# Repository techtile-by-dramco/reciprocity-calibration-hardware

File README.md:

# Techtile PLL board ✅

This PCB was developed by Guus Leenders from KU Leuven, in collaboration with DRAMCO, with assistance from Jarne Van Mulders. The board is utilized in a distributed antenna or **Radioweave** infrastructure and delivers a phase-synchronous RF output to the USRP by means of a PPS and 10MHz signal. 

❗❗ This board is specifically designed for the **USRP B210** by Ettus. ❗❗

The PPS and 10MHz signals (coming from the octoclocks CDA2990) are amplified using on board buffers and are connected to the
* PLL IC (MAX287x) ❗❗ **--> allowing for ∿ phase synchronisation ∿**
* the flat cable connector (given that the raspberry pi also has access to these signals) ❗
* the input SMA connectors of the USRPs intself ❗❗
  * ** 10 MHz --> ∿ frequency synchronisation ∿ for internal (RF) PLLs**
  * ** PPS --> ⏰ time synchronisation ⏰**

The board is controlled via I2C commands and features a flat cable input connected to the RPI HAT (developed by DRAMCO) to drive the PLL output. The most important registers are displayed below.

###  PLL board general settings ⚙️

|Register name| byte |
|--|--|
|REGISTER_SETTINGS_DEVICE_ID            | 0x00 |
|REGISTER_SETTINGS_HARDWARE_VERSION     | 0x01 |
|REGISTER_SETTINGS_FIRMWARE_VERSION     | 0x02 |
|REGISTER_SETTINGS_SAVE_TO_EEPROM       | 0x03 |
|REGISTER_SETTINGS_PLL_REFERENCE_CLOCK  | 0x04 |
|REGISTER_SETTINGS_PLL_REFERENCE_DIVIDER| 0x06 |
|REGISTER_SETTINGS_LED_MODE             | 0x07 |
|REGISTER_SETTINGS_LED_BLINK_ON_TIME    | 0x08 |
|REGISTER_SETTINGS_LED_BLINK_OFF_TIME   | 0x09 |

###  PLL (MAX287x) settings ⚙️

|Register name| byte | Remarks |
|--|--|--|
|REGISTER_PLL_POWER                     | 0x10 | |
|REGISTER_PLL_FREQUENCY                 | 0x11 | 2 byte (uint16) |
|REGISTER_PLL_ENABLE_OUTPUT             | 0x13 | |
|REGISTER_PLL_LOCK_DETECTED             | 0x14 | Read only |
|REGISTER_PLL_MODE                      | 0x15 | Read only |

# Phase synchronisation in Techtile ToDo 📝
- Work further on python script to achieve phase-synchronised outputs with the B210 USRP. Validate and visualize the signals on the oscilloscope by using two separate setups consisting of RPI, USRP, PLL, PPS, and 10 MHz input.
- Current status ⏳ PENDING ⏳

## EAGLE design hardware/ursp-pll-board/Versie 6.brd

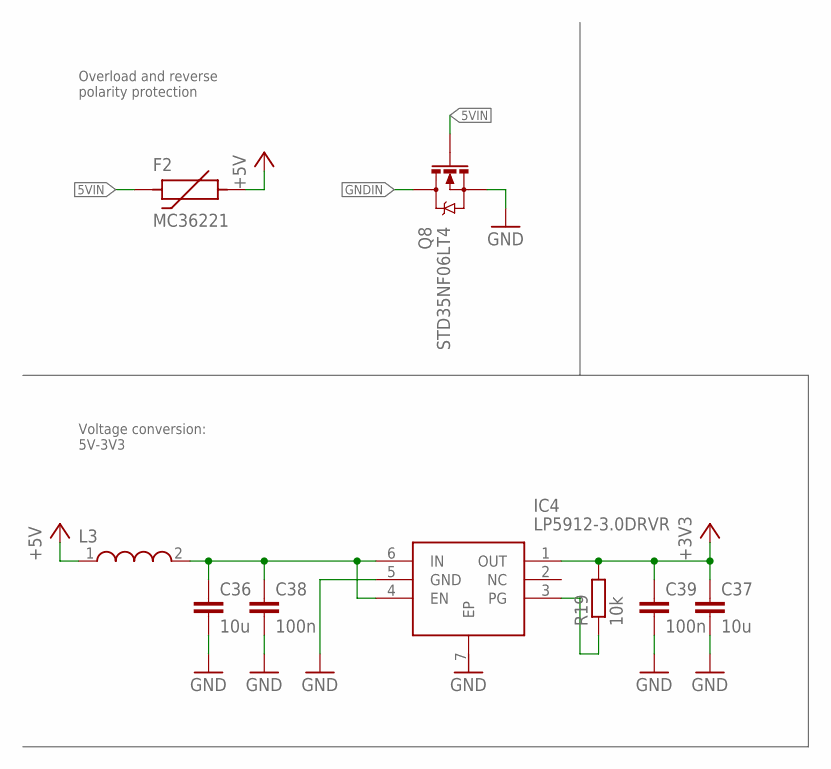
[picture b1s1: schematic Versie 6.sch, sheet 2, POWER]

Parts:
C36, C37: 10u; C0603
C38, C39: 100n; C0603
F2: MC36221; 1206
IC4: LP5912-3.0DRVR; SON65P200X200X80-7N
L3: WE-CBA_0603(WB/HS); WE-CBA_0603(W=2.2)
Q8: STD35NF06LT4; SOT23-3
R19: 10k; R0603

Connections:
5VIN: F2.P$1, Q8.1 (G); also elsewhere on the board
+3V3: C37.1, C39.1, IC4.1 (OUT), R19.2; also elsewhere on the board
+5V: F2.P$2, L3.1
GND: C36.2, C37.2, C38.2, C39.2, IC4.5 (GND), Q8.2 (S); also elsewhere on the board
GNDIN: Q8.3 (D); also elsewhere on the board
unnamed: C36.1, C38.1, IC4.4 (EN), IC4.6 (IN), L3.2
unnamed: IC4.3 (PG), R19.1

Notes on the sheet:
Overload and reverse polarity protection
Voltage conversion: 5V-3V3

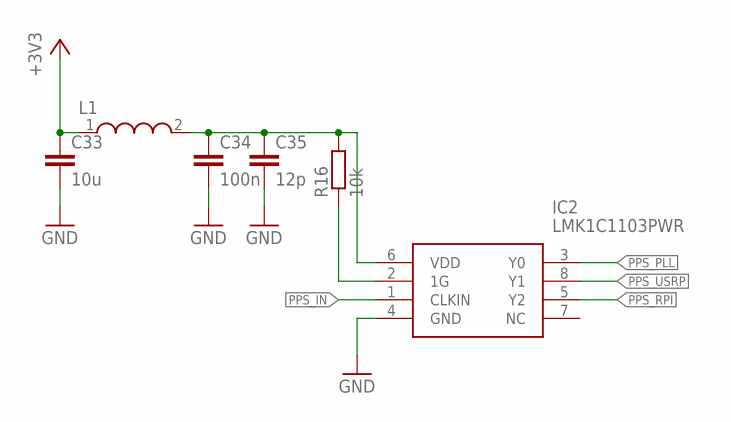
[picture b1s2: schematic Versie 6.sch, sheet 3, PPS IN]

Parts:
C33: 10u; C0603
C34: 100n; C0603
C35: 12p; C0603
IC2: LMK1C1103PWR; SOP65P640X120-8N
L1: WE-CBA_0603(WB/HS); WE-CBA_0603(W=2.2)
R16: 10k; R0603

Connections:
+3V3: C33.1, L1.1; also elsewhere on the board
GND: C33.2, C34.2, C35.2, IC2.4 (GND); also elsewhere on the board
unnamed: IC2.2 (1G), R16.1
unnamed: C34.1, C35.1, IC2.6 (VDD), L1.2, R16.2
PPS_IN: IC2.1 (CLKIN); also elsewhere on the board
PPS_PLL: IC2.3 (Y0); also elsewhere on the board
PPS_RPI: IC2.5 (Y2); also elsewhere on the board
PPS_USRP: IC2.8 (Y1); also elsewhere on the board

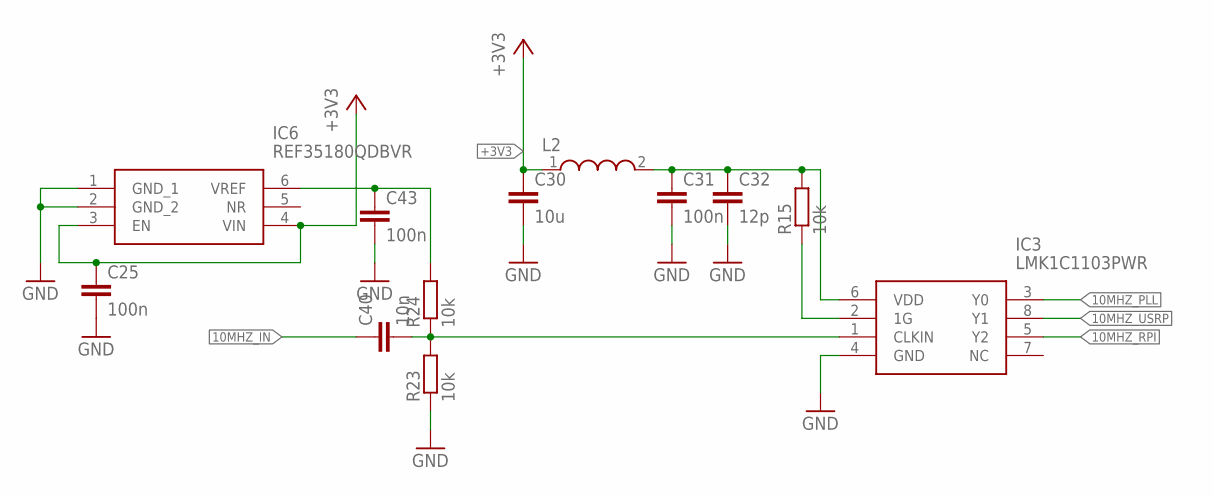
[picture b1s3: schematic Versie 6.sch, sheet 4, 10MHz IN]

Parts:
C25, C31, C43: 100n; C0603
C30: 10u; C0603
C32: 12p; C0603
C40: 10n; C0603
IC3: LMK1C1103PWR; SOP65P640X120-8N
IC6: REF35180QDBVR; SOT95P280X145-6N
L2: WE-CBA_0603(WB/HS); WE-CBA_0603(W=2.2)
R15, R23, R24: 10k; R0603

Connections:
10MHZ_IN: C40.1; also elsewhere on the board
10MHZ_PLL: IC3.3 (Y0); also elsewhere on the board
10MHZ_RPI: IC3.5 (Y2); also elsewhere on the board
10MHZ_USRP: IC3.8 (Y1); also elsewhere on the board
+3V3: C25.1, C30.1, IC6.3 (EN), IC6.4 (VIN), L2.1; also elsewhere on the board
GND: C25.2, C30.2, C31.2, C32.2, C43.2, IC3.4 (GND), IC6.1 (GND_1), IC6.2 (GND_2), R23.1; also elsewhere on the board
unnamed: C40.2, IC3.1 (CLKIN), R23.2, R24.1
unnamed: IC3.2 (1G), R15.1
unnamed: C31.1, C32.1, IC3.6 (VDD), L2.2, R15.2
unnamed: C43.1, IC6.6 (VREF), R24.2

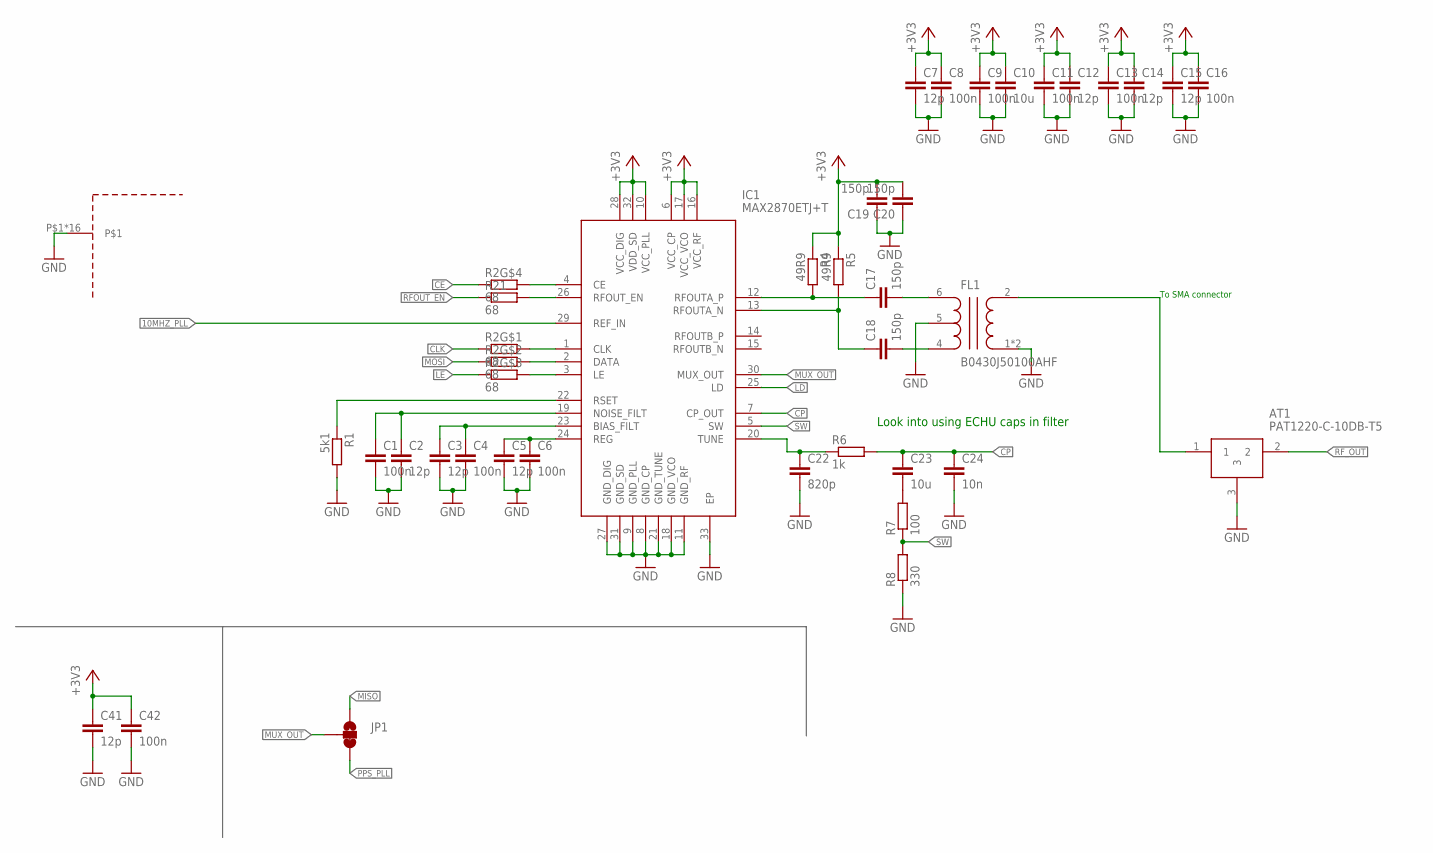
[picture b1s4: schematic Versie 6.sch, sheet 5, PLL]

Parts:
AT1: PAT1220-C-10DB-T5; PAT1220C10DBT5
C1, C4, C6, C8, C9, C11, C13, C16, C42: 100n; C0603
C2, C3, C5, C7, C12, C14, C15, C41: 12p; C0603
C10, C23: 10u; C0603
C17, C18, C19, C20: 150p; C0402
C22: 820p; C0603
C24: 10n; C0603
FL1: B0430J50100AHF
IC1: MAX2870ETJ+T; QFN50P500X500X80-33N
JP1: JUMPER-SMT_3_1-NC_TRACE_SILK; SMT-JUMPER_3_1-NC_TRACE_SILK
R1: 5k1; R0603
R2: 68; CAY16A1003F4LF
R4, R5: 49R9; R0402
R6: 1k; R0603
R7: 100; R0603
R8: 330; R0603
R21: 68; R0603
U$1: BMI-S-209-F-20-R

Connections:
10MHZ_PLL: IC1.29 (REF_IN); also elsewhere on the board
+3V3: C7.1, C8.1, C9.1, C10.1, C11.1, C12.1, C13.1, C14.1, C15.1, C16.1, C19.2, C20.2, C41.1, C42.1, IC1.6 (VCC_CP), IC1.10 (VCC_PLL), IC1.16 (VCC_RF), IC1.17 (VCC_VCO), IC1.28 (VCC_DIG), IC1.32 (VDD_SD), R4.1, R5.1; also elsewhere on the board
CE: R2.4 (1); also elsewhere on the board
CLK: R2.1; also elsewhere on the board
CP: C23.1, C24.1, IC1.7 (CP_OUT), R6.2
GND: AT1.3, C1.2, C2.2, C3.2, C4.2, C5.2, C6.2, C7.2, C8.2, C9.2, C10.2, C11.2, C12.2, C13.2, C14.2, C15.2, C16.2, C19.1, C20.1, C22.2, C24.2, C41.2, C42.2, FL1.1 (GND_1), FL1.3 (GND_1), FL1.5 (NC), IC1.8 (GND_CP), IC1.9 (GND_PLL), IC1.11 (GND_RF), IC1.18 (GND_VCO), IC1.21 (GND_TUNE), IC1.27 (GND_DIG), IC1.31 (GND_SD), IC1.33 (EP), R1.2, R8.1, U$1.P$1, U$1.P$2, U$1.P$3, U$1.P$4, U$1.P$5, U$1.P$6, U$1.P$7, U$1.P$8, U$1.P$9, U$1.P$10, U$1.P$11, U$1.P$12, U$1.P$13, U$1.P$14, U$1.P$15, U$1.P$16; also elsewhere on the board
LD: IC1.25 (LD); also elsewhere on the board
LE: R2.3 (1); also elsewhere on the board
MISO: JP1.1; also elsewhere on the board
MOSI: R2.2 (1); also elsewhere on the board
MUX_OUT: IC1.30 (MUX_OUT), JP1.2
unnamed: C5.1, C6.1, IC1.24 (REG)
unnamed: IC1.22 (RSET), R1.1
unnamed: IC1.1 (CLK), R2.8 (2)
unnamed: IC1.2 (DATA), R2.7 (2)
unnamed: IC1.3 (LE), R2.6 (2)
unnamed: C1.1, C2.1, IC1.19 (NOISE_FILT)
unnamed: C3.1, C4.1, IC1.23 (BIAS_FILT)
unnamed: IC1.26 (RFOUT_EN), R21.2
unnamed: IC1.4 (CE), R2.5 (2)
unnamed: C22.1, IC1.20 (TUNE), R6.1
unnamed: C17.1, IC1.12 (RFOUTA_P), R4.2
unnamed: C18.1, IC1.13 (RFOUTA_N), R5.2
unnamed: C18.2, FL1.4 (BALANCED_PORT_1)
unnamed: C17.2, FL1.6 (BALANCED_PORT_2)
unnamed: C23.2, R7.2
unnamed: AT1.1, FL1.2 (UNBALANCED)
PPS_PLL: JP1.3; also elsewhere on the board
RFOUT_EN: R21.1; also elsewhere on the board
RF_OUT: AT1.2; also elsewhere on the board
SW: IC1.5 (SW), R7.1, R8.2

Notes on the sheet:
To SMA connector
Look into using ECHU caps in filter

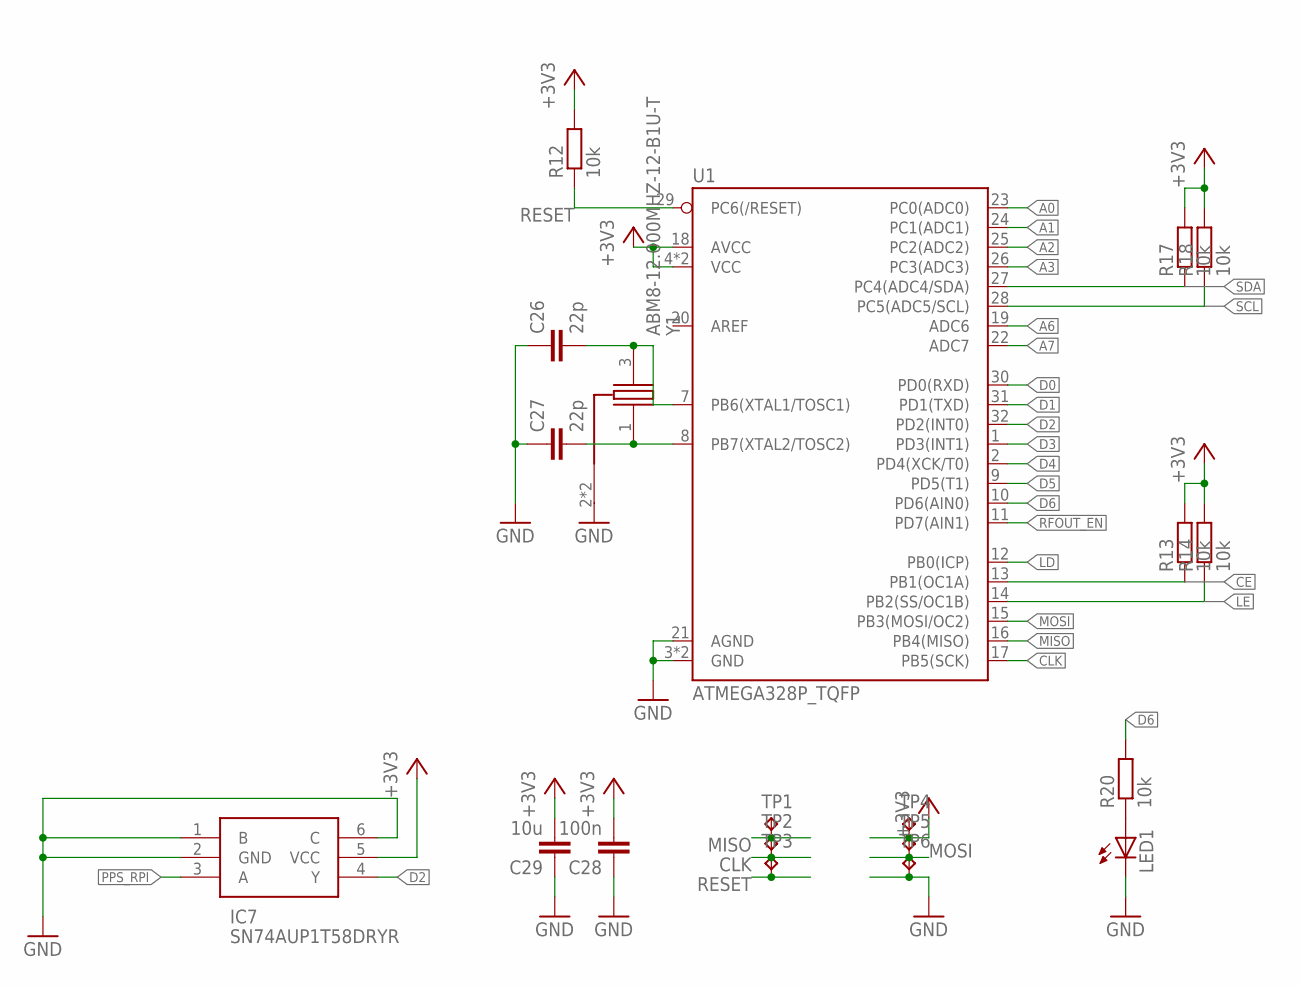
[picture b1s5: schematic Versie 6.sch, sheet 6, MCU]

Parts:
C26, C27: 22p; C0603
C28: 100n; C0603
C29: 10u; C0603
IC7: SN74AUP1T58DRYR; SON50P100X145X60-6N
LED1: LEDCHIPLED_0805; CHIPLED_0805
R12, R13, R14, R17, R18, R20: 10k; R0603
TP1, TP2, TP3, TP4, TP5, TP6: TPTP16R; TP16R
U1: ATMEGA328P_TQFP; TQFP32-08
Y1: ABM8-12.000MHZ-12-B1U-T; ABM810000MHZ12D2W

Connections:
+3V3: C28.2, C29.2, IC7.5 (VCC), R12.2, R13.2, R14.2, R17.2, R18.2, TP4.TP, U1.4 (VCC), U1.6 (VCC), U1.18 (AVCC); also elsewhere on the board
A0: U1.23 (PC0(ADC0)); also elsewhere on the board
A1: U1.24 (PC1(ADC1)); also elsewhere on the board
A2: U1.25 (PC2(ADC2)); also elsewhere on the board
A3: U1.26 (PC3(ADC3)); also elsewhere on the board
A6: U1.19 (ADC6)
A7: U1.22 (ADC7)
CE: R13.1, U1.13 (PB1(OC1A)); also elsewhere on the board
CLK: TP2.TP, U1.17 (PB5(SCK)); also elsewhere on the board
D0: U1.30 (PD0(RXD)); also elsewhere on the board
D1: U1.31 (PD1(TXD)); also elsewhere on the board
D2: IC7.4 (Y), U1.32 (PD2(INT0))
D3: U1.1 (PD3(INT1)); also elsewhere on the board
D4: U1.2 (PD4(XCK/T0)); also elsewhere on the board
D5: U1.9 (PD5(T1))
D6: R20.2, U1.10 (PD6(AIN0))
GND: C26.1, C27.1, C28.1, C29.1, IC7.1 (B), IC7.2 (GND), IC7.6 (C), LED1.C, TP6.TP, U1.3 (GND), U1.5 (GND), U1.21 (AGND), Y1.2 (GND_1), Y1.4 (GND_1); also elsewhere on the board
LD: U1.12 (PB0(ICP)); also elsewhere on the board
LE: R14.1, U1.14 (PB2(SS/OC1B)); also elsewhere on the board
MISO: TP1.TP, U1.16 (PB4(MISO)); also elsewhere on the board
MOSI: TP5.TP, U1.15 (PB3(MOSI/OC2)); also elsewhere on the board
unnamed: LED1.A, R20.1
unnamed: C26.2, U1.7 (PB6(XTAL1/TOSC1)), Y1.3 (X2)
unnamed: C27.2, U1.8 (PB7(XTAL2/TOSC2)), Y1.1 (X1)
PPS_RPI: IC7.3 (A); also elsewhere on the board
RESET: R12.1, TP3.TP, U1.29 (PC6(/RESET))
RFOUT_EN: U1.11 (PD7(AIN1)); also elsewhere on the board
SCL: R18.1, U1.28 (PC5(ADC5/SCL)); also elsewhere on the board
SDA: R17.1, U1.27 (PC4(ADC4/SDA)); also elsewhere on the board

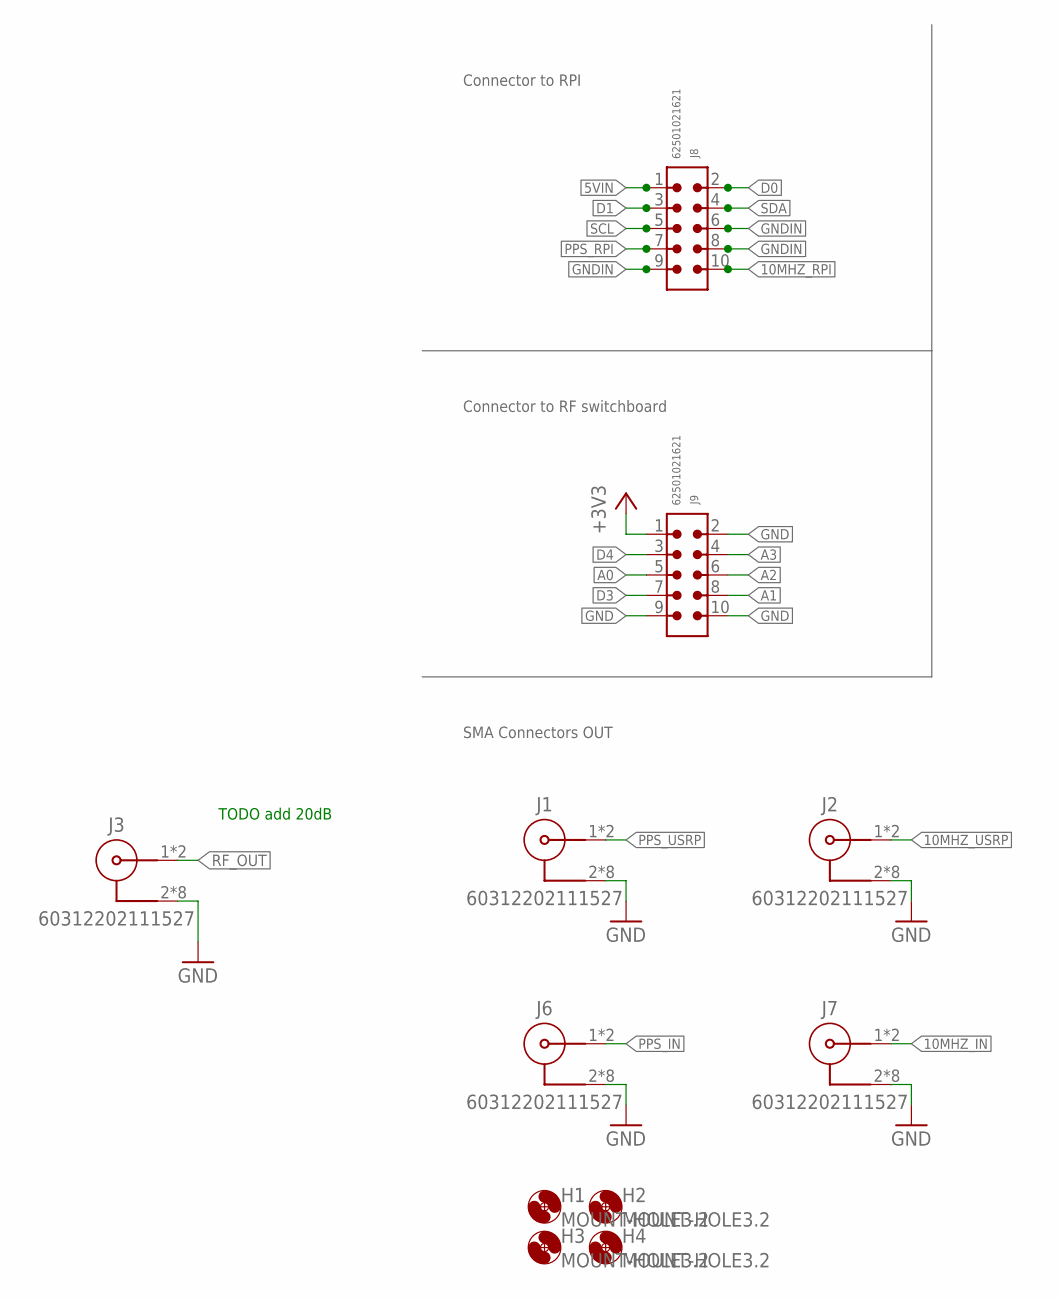
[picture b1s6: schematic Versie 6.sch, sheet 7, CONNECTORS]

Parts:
H1, H2, H3, H4: MOUNT-HOLE3.2; 3,2
J1, J2, J3, J6, J7: 60312202111527
J8, J9: 62501021621

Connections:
5VIN: J8.1; also elsewhere on the board
10MHZ_IN: J7.1, J7.6 (1); also elsewhere on the board
10MHZ_RPI: J8.10; also elsewhere on the board
10MHZ_USRP: J2.1, J2.6 (1); also elsewhere on the board
+3V3: J9.1; also elsewhere on the board
A0: J9.5; also elsewhere on the board
A1: J9.8; also elsewhere on the board
A2: J9.6; also elsewhere on the board
A3: J9.4; also elsewhere on the board
D0: J8.2; also elsewhere on the board
D1: J8.3; also elsewhere on the board
D3: J9.7; also elsewhere on the board
D4: J9.3; also elsewhere on the board
GND: J1.2, J1.3 (2), J1.4 (2), J1.5 (2), J1.7 (2), J1.8 (2), J1.9 (2), J1.10 (2), J2.2, J2.3 (2), J2.4 (2), J2.5 (2), J2.7 (2), J2.8 (2), J2.9 (2), J2.10 (2), J3.2, J3.3 (2), J3.4 (2), J3.5 (2), J3.7 (2), J3.8 (2), J3.9 (2), J3.10 (2), J6.2, J6.3 (2), J6.4 (2), J6.5 (2), J6.7 (2), J6.8 (2), J6.9 (2), J6.10 (2), J7.2, J7.3 (2), J7.4 (2), J7.5 (2), J7.7 (2), J7.8 (2), J7.9 (2), J7.10 (2), J9.2, J9.9, J9.10; also elsewhere on the board
GNDIN: J8.6, J8.8, J8.9; also elsewhere on the board
PPS_IN: J6.1, J6.6 (1); also elsewhere on the board
PPS_RPI: J8.7; also elsewhere on the board
PPS_USRP: J1.1, J1.6 (1); also elsewhere on the board
RF_OUT: J3.1, J3.6 (1); also elsewhere on the board
SCL: J8.5; also elsewhere on the board
SDA: J8.4; also elsewhere on the board

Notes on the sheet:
Connector to RPI
Connector to RF switchboard
SMA Connectors OUT
TODO add 20dB

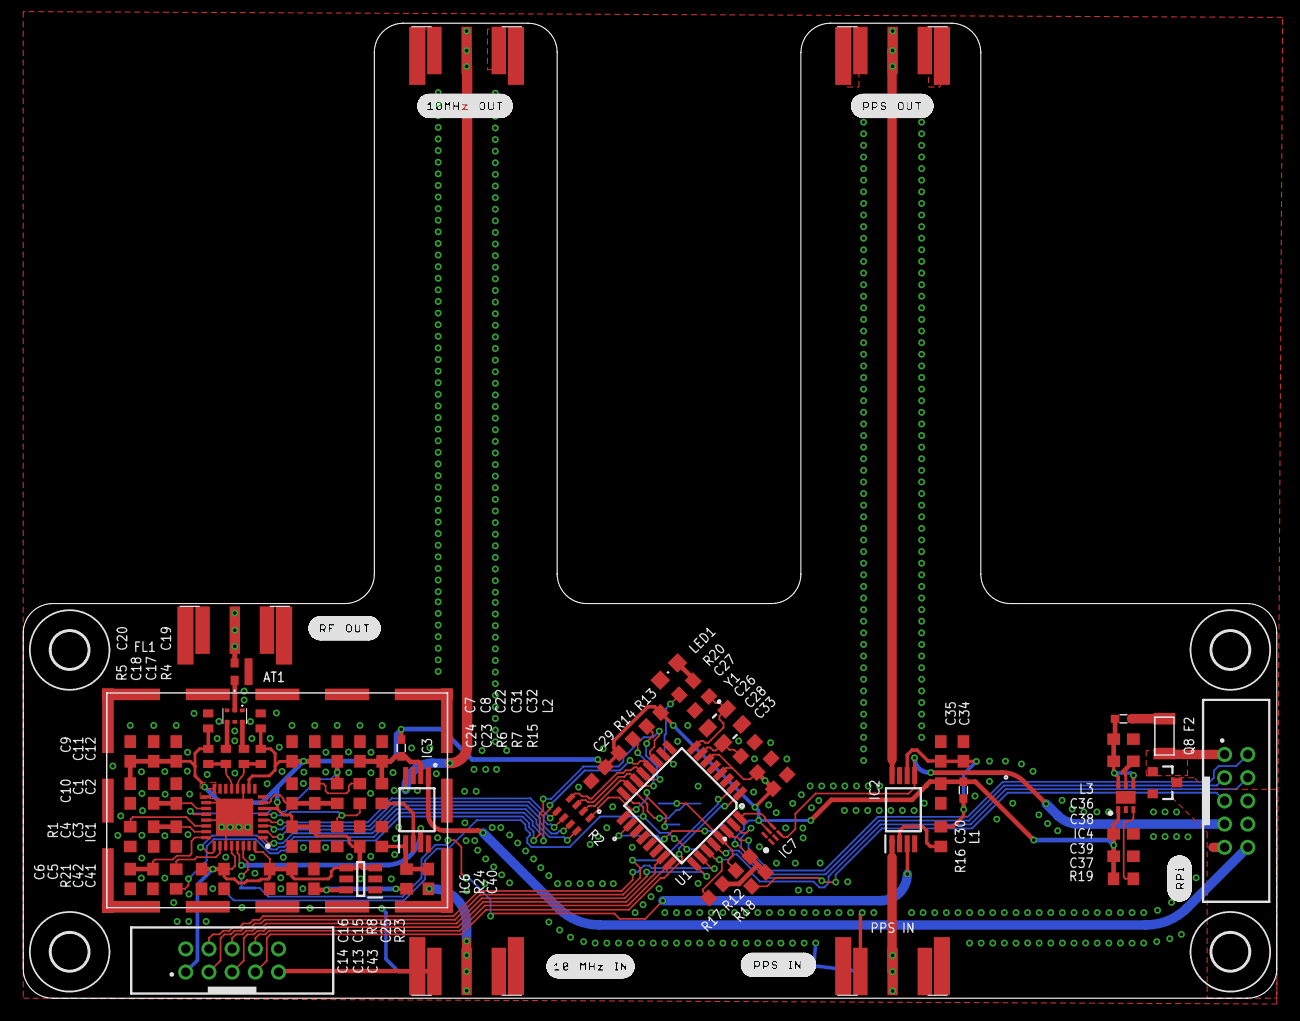
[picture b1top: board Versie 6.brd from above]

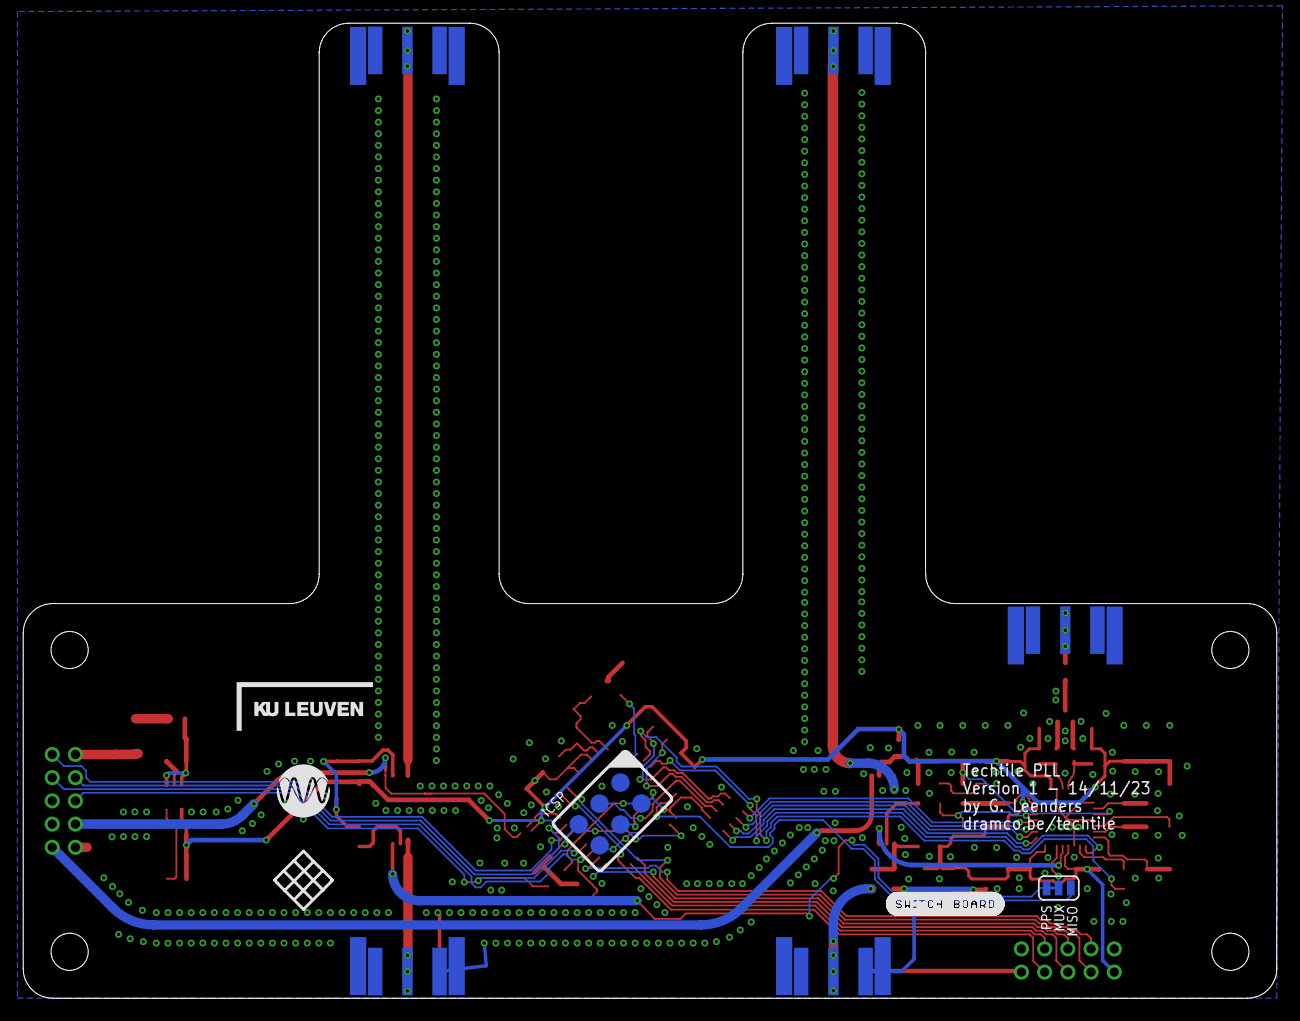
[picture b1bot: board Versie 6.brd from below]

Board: 2 copper layers, 108.0 x 84.0 mm, 96 parts (7 on the bottom side), 64 nets.

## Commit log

2024-03-19 Added switch board firmware
2024-04-05 Redesigned board and expanded firmware
2024-04-05 Changed values of loop filter
2024-05-06 Bug fixes
2024-05-13 added python lib
2024-05-13 fixed duplicate name of method and attribute frequency
2024-05-15 make it installable
2024-05-15 update package

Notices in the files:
parts and their libraries:
Eagle_WR-SMA: Copyright: Würth Elektronik
SparkFun-Jumpers: Licensing: Creative Commons ShareAlike 4.0 International - https://creativecommons.org/licenses/by-sa/4.0
